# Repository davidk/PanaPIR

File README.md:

# Panasonic PIR breakout board

This is a Panasonic PIR breakout board. It breaks out their TO-5 sensors onto 0.1"/2.54mm pitch headers, for use with a solderless breadboard.

Here is what it looks like currently:

Top (alongside the EKMC1601111):

Rear (note the filled in gold area on one pin of the PIR, it goes with the \* on the board and denotes ground):

## Fabrication

The simplest way is to just [click through to this shared project on OSHPark's site](http://oshpark.com/shared_projects/VIIMKRcy). You'll get three boards with purple soldermask.

If you prefer using your own CNC/mill/board house, just grab the Gerber files and KiCAD source and bobs (nearly) your uncle. If you really are going to use a CNC/mill/etch, it might be ideal to drop a polygon fill on both sides to minimize the amount of copper that needs to be removed.

### Bill of Materials

Pick a sensor (these have been verified to fit on this breakout):

| Model       | Vendor |
| ----------- | ------ |
| EKMB1303112 | [Mouser](http://www.mouser.com/Search/Refine.aspx?Keyword=EKMB1303112) |
| EKMC1601111 | [Digikey](http://www.digikey.com/product-search/en?WT.z_header=search_go&lang=en&site=us&keywords=EKMC1601111) |

You'll also need a strip of 0.1"/2.54mm header, but this is optional (since you may use wire to permanently 
install the breakout later).

| Quantity | Description/Vendor |
| -------- | ------------------ |
| 1        | 36-pin header: [Mouser: 649-68004-236](http://www.mouser.com/Search/Refine.aspx?Keyword=649-68004-236) / Alternative (3-pin, untested!): [Mouser: 571-1031853](http://www.mouser.com/Search/Refine.aspx?Keyword=571-1031853) |

## Licensing

CC0 1.0 Universal (the LICENSE file has more details)

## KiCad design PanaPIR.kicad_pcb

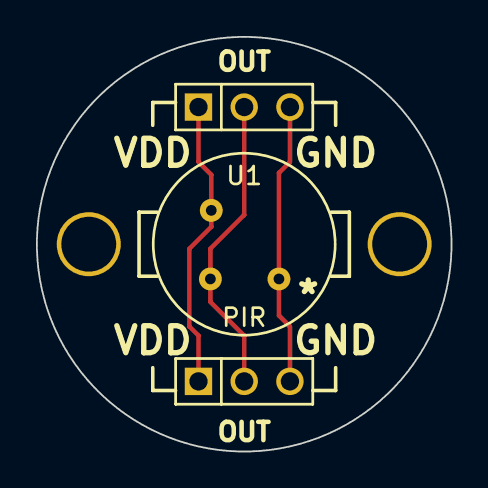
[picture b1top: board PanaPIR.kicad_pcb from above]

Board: 2 copper layers, 23.0 x 23.0 mm, 5 parts (0 on the bottom side), 3 nets.

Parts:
1PIN, 1PIN#2: P***; 3mm_mounting
P1, P2: HEADER; PIN_ARRAY_3X1
U1: PIR

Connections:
unnamed: P1.3, P2.3, U1.3
unnamed: P1.2, P2.2, U1.2
unnamed: P1.1, P2.1, U1.1

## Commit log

2014-03-30 Update the README with new name and license
2014-03-30 Add KiCAD files from previous git repository
    This still retains the short git commit hash written on the back
    of the PCB (mask layer) from that repository.
2014-03-31 Add board image
2014-03-31 Move images to pictures/
2014-03-31 Add picture
    Closes #2
    This will likely redone in the future with the actual sensor in the photo.
2014-03-31 Add KiCAD generated gerbers.
    These gerbers were used for fabrication with OSHPark, and
    have export parameters tuned to their requirements.
    closes #1
2014-03-31 Generate a zip file of gerbers for upload to OSHPark
    Genereated from files in commit: 5116fca
2014-04-09 In development notes
2014-04-15 Validate EKMC1601111
2014-04-20 Make PCB more compatible with breadboards
2014-04-20 2014-04-08 production gerbers
2014-04-20 Zipped gerbers from eabde8d
2014-04-20 Add 0603 decoupling cap and better spacing for breadboards
    600 mil center drill distance from top to bottom for PTH headers.
2014-04-20 Out of active development
2014-04-21 Go go gadget release documentation
2014-04-21 Go go gadget table update and fix!
2014-04-21 Notes
2014-04-29 Remove older board photo and add new ones
2014-04-29 Scale top side picture down a bit
2014-04-29 Update photos with current breakout
2014-04-29 Update image descriptions
2014-04-29 More board notes
